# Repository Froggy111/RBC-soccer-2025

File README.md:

# RBC-soccer-2025

(Currently internal) Repository for 2025 RCJ Soccer Lightweight team from RI.

Other Links:
- Component spreadsheet: https://docs.google.com/spreadsheets/d/1nkJU1fMwBykuh6vTQhCEh5VCzHdAhULuCZyUjWnpDP0/edit#gid=0

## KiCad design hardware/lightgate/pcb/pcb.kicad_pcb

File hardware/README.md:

- `./*.md`: General Information about Hardware
- `./{component}/*.md`: Information about a specific component

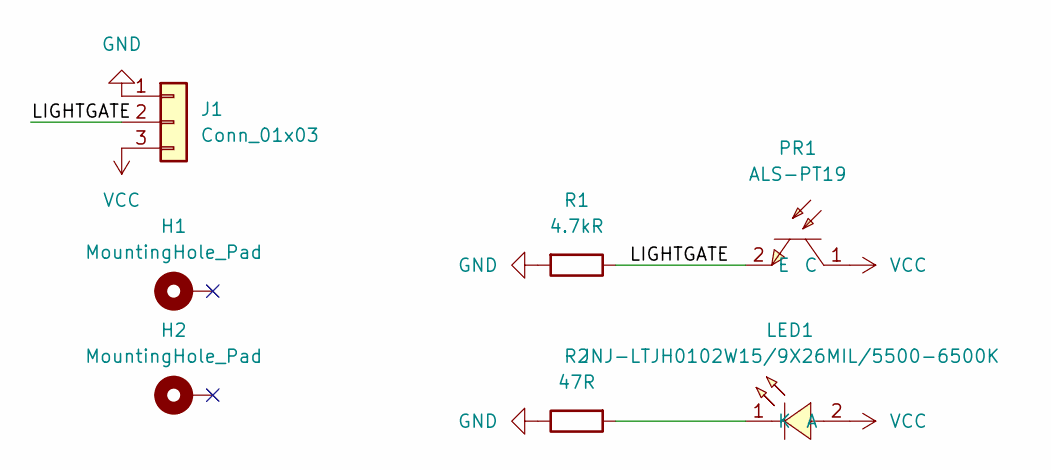
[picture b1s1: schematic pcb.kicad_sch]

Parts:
H1, H2: MountingHole_Pad; MountingHole_2.2mm_M2_Pad_Via
J1: Conn_01x03; JST_XH_B3B-XH-A_1x03_P2.50mm_Vertical
LED1: JNJ-LTJH0102W15/9X26MIL/5500-6500K; LED-SMD_L3.5-W2.8_JNJ-LTJH0111W60; LCSC Part C7500117
PR1: ALS-PT19; SENSORS-SMD_ALS-PT19; LCSC Part C146233
R1: 4.7kR; R_1206_3216Metric_Pad1.30x1.75mm_HandSolder
R2: 47R; R_1206_3216Metric_Pad1.30x1.75mm_HandSolder

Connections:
/LIGHTGATE: J1.2, PR1.2 (E), R1.1
GND: J1.1, R1.2, R2.1
unnamed: LED1.1 (K), R2.2
VCC: J1.3, LED1.2 (A), PR1.1 (C)

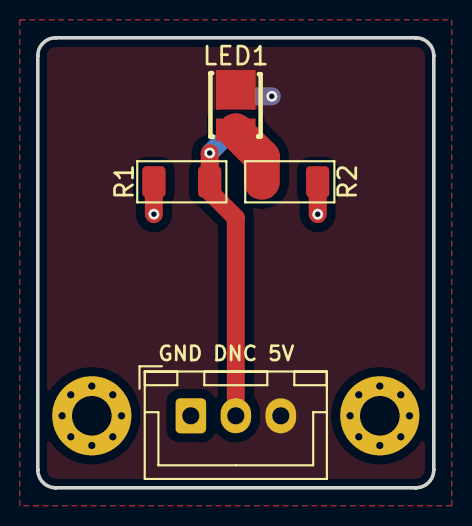
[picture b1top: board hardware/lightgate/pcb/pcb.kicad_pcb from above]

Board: 2 copper layers, 22.0 x 25.0 mm, 7 parts (1 on the bottom side), 4 nets.

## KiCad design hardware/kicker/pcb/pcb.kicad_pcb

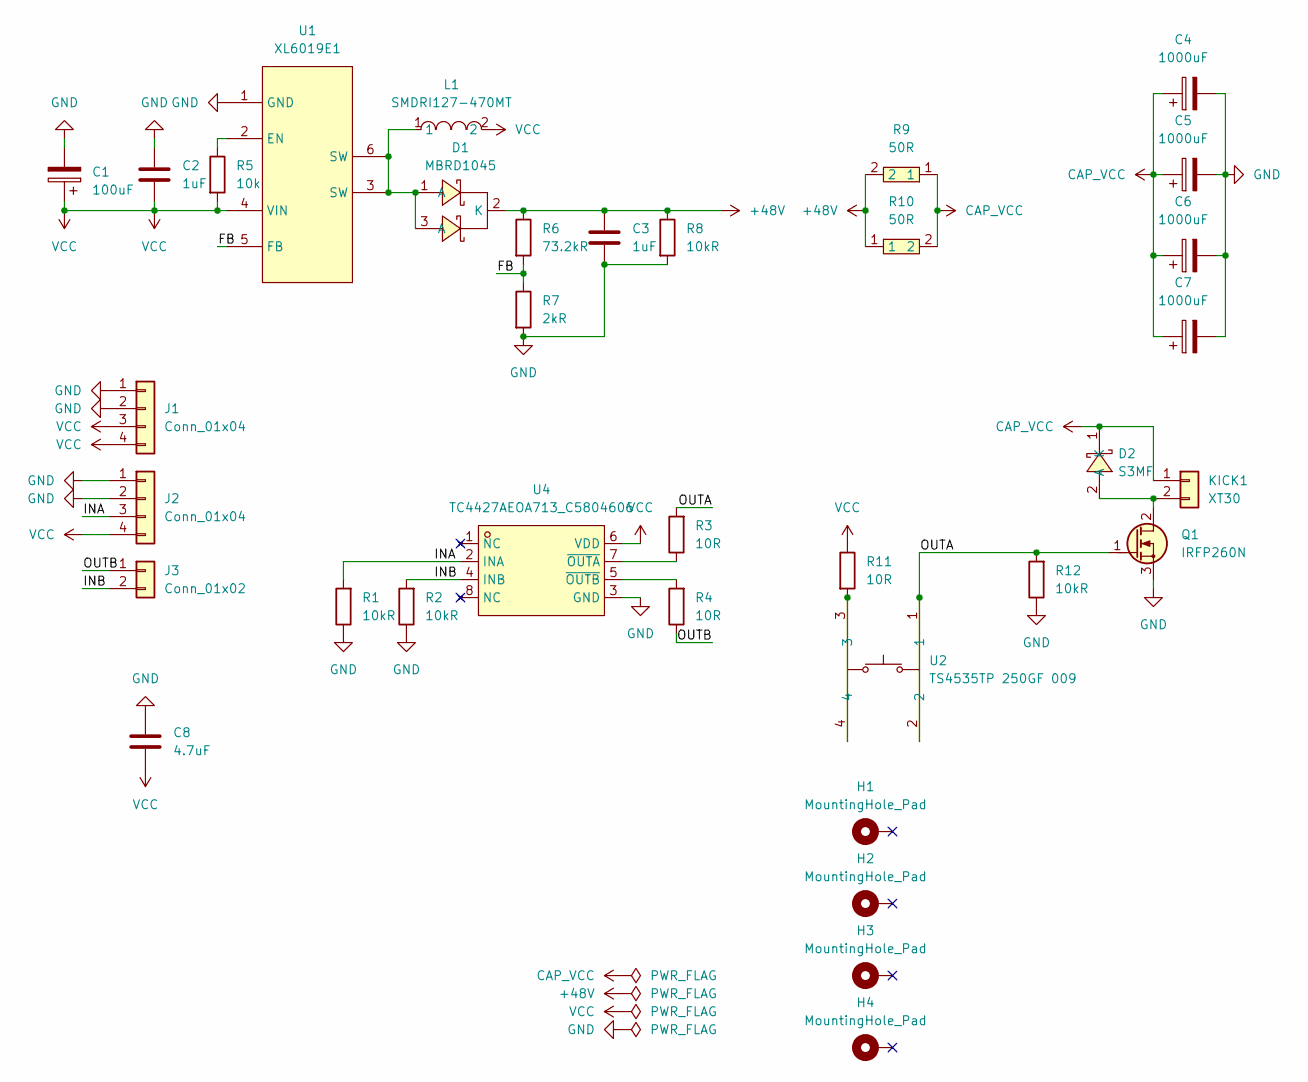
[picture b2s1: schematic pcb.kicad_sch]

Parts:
C1: 100uF; CP_Elec_6.3x7.7
C2, C3: 1uF; C_1206_3216Metric_Pad1.33x1.80mm_HandSolder
C4, C5, C6, C7: 1000uF; CAP-TH_BD13.0-P5.00-D1.2-FD
C8: 4.7uF; C_1206_3216Metric_Pad1.33x1.80mm_HandSolder
D1: MBRD1045; TO-252-3_L6.5-W5.9-P4.60-LS10.0-BL; LCSC Part C5137764
D2: S3MF; SMAF_L3.5-W2.6-LS4.7-RD-1; LCSC Part C18199092
H1, H2, H3, H4: MountingHole_Pad; MountingHole_2.2mm_M2_Pad_Via
J1, J2: Conn_01x04; PinHeader_1x04_P2.54mm_Vertical
J3: Conn_01x02; JST_PH_B2B-PH-K_1x02_P2.00mm_Vertical
KICK1: XT30; AMASS_XT30U-F_1x02_P5.0mm_Vertical
L1: SMDRI127-470MT; IND-SMD_L12.3-W12.3; LCSC Part C9906
Q1: IRFP260N; TO-247-3_Vertical_GDS
R1, R2, R8, R12: 10kR; R_1206_3216Metric_Pad1.30x1.75mm_HandSolder
R3, R4, R11: 10R; R_1206_3216Metric_Pad1.30x1.75mm_HandSolder
R5: 10k; R_1206_3216Metric_Pad1.30x1.75mm_HandSolder
R6: 73.2kR; R_1206_3216Metric_Pad1.30x1.75mm_HandSolder
R7: 2kR; R_1206_3216Metric_Pad1.30x1.75mm_HandSolder
R9, R10: 50R; TO-220-2L_L10.2-W4.6-P5.08-L; LCSC Part C5209737
U1: XL6019E1; TO-263-5_L10.2-W9.9-P1.70-LS14.4-TL; LCSC Part C73018
U2: TS4535TP 250GF 009; SW-SMD_4P-L4.5-W4.5-P3.00-LS6.8; LCSC Part C5342982
U4: TC4427AEOA713_C5804606; SOIC-8_L4.9-W3.9-P1.27-LS6.0-BL; LCSC Part C5804606

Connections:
+48V: C3.1, D1.2 (K), R6.1, R8.1, R9.2, R10.1
/FB: R6.2, R7.1, U1.5 (FB)
/INA: J2.3, R1.2, U4.2 (INA)
/INB: J3.2, R2.2, U4.4 (INB)
/OUTA: Q1.1 (G), R3.2, R12.2, U2.1, U2.2
/OUTB: J3.1, R4.1
CAP_VCC: C4.1, C5.1, C6.1, C7.1, D2.1 (K), KICK1.1, R9.1, R10.2
GND: C1.2, C2.1, C3.2, C4.2, C5.2, C6.2, C7.2, C8.1, J1.1, J1.2, J2.1, J2.2, Q1.3 (S), R1.1, R2.1, R7.2, R8.2, R12.1, U1.1 (GND), U4.3 (GND)
unnamed: D1.1 (A), D1.3 (A), L1.1, U1.3 (SW), U1.6 (SW)
unnamed: D2.2 (A), KICK1.2, Q1.2 (D)
unnamed: R11.2, U2.3, U2.4
unnamed: R5.1, U1.2 (EN)
unnamed: R3.1, U4.7 (~OUTA)
unnamed: R4.2, U4.5 (~OUTB)
VCC: C1.1, C2.2, C8.2, J1.3, J1.4, J2.4, L1.2, R5.2, R11.1, U1.4 (VIN), U4.6 (VDD)

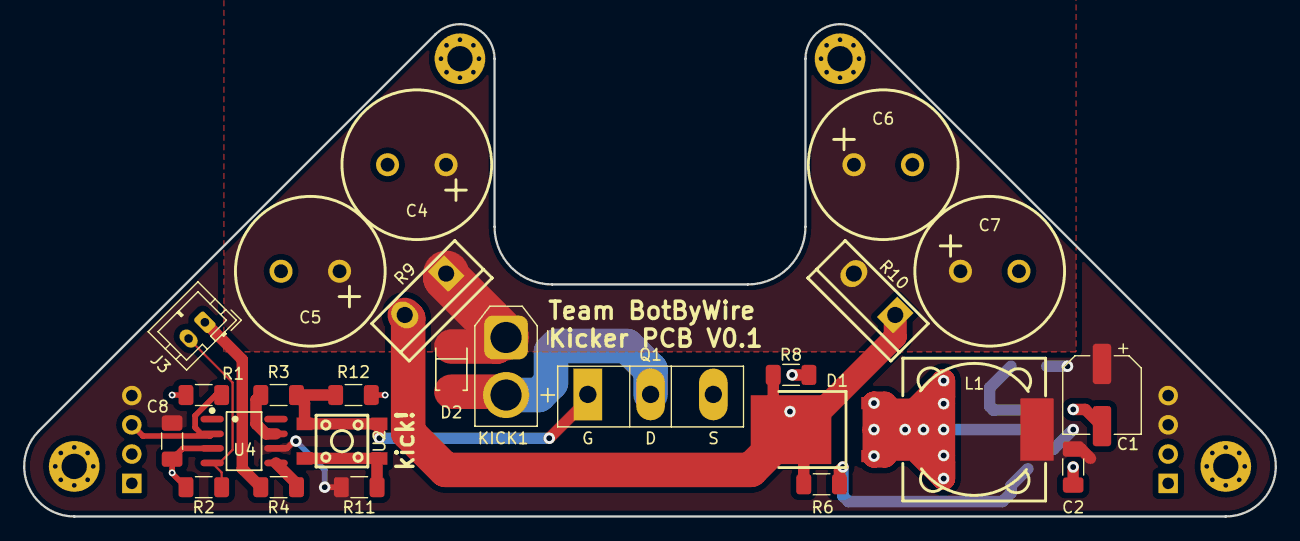
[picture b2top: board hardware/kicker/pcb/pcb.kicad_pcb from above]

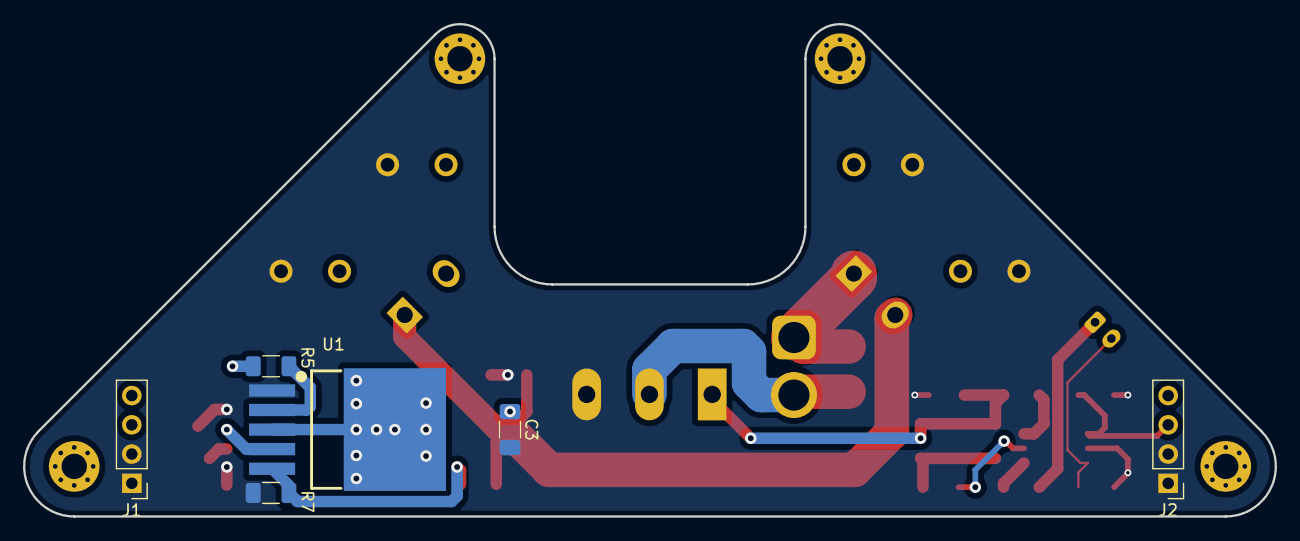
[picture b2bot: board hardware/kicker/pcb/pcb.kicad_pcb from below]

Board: 2 copper layers, 108.7 x 42.8 mm, 35 parts (6 on the bottom side), 15 nets.

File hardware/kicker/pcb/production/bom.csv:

Designator,Footprint,Quantity,Value,LCSC Part #
C1,CP_Elec_6.3x7.7,1,100uF,
"C2, C3",1206,2,1uF,
"C4, C5, C6, C7",CAP-TH_BD13.0-P5.00-D1.2-FD,4,1000uF,
C8,1206,1,4.7uF,
D1,TO-252-3_L6.5-W5.9-P4.60-LS10.0-BL,1,MBRD1045,C5137764
D2,SMAF_L3.5-W2.6-LS4.7-RD-1,1,S3MF,C18199092
"J1, J2",PinHeader_1x04_P2.54mm_Vertical,2,Conn_01x04,
J3,JST_PH_B2B-PH-K_1x02_P2.00mm_Vertical,1,Conn_01x02,
KICK1,AMASS_XT30U-F_1x02_P5.0mm_Vertical,1,XT30,
L1,IND-SMD_L12.3-W12.3,1,SMDRI127-470MT,C9906
Q1,TO-247-3_Vertical,1,NMOS,
"R1, R11, R12, R2, R8",1206,5,10kR,
"R10, R9",TO-220-2L_L10.2-W4.6-P5.08-L,2,50R,C5209737
"R3, R4",1206,2,10R,
R5,1206,1,10k,
R6,1206,1,73.2kR,
R7,1206,1,2kR,
U1,TO-263-5_L10.2-W9.9-P1.70-LS14.4-TL,1,XL6019E1,C73018
U2,SW-SMD_4P-L4.5-W4.5-P3.00-LS6.8,1,TS4535TP 250GF 009,C5342982
U4,SOIC-8_L4.9-W3.9-P1.27-LS6.0-BL,1,TC4427AEOA713_C5804606,C5804606

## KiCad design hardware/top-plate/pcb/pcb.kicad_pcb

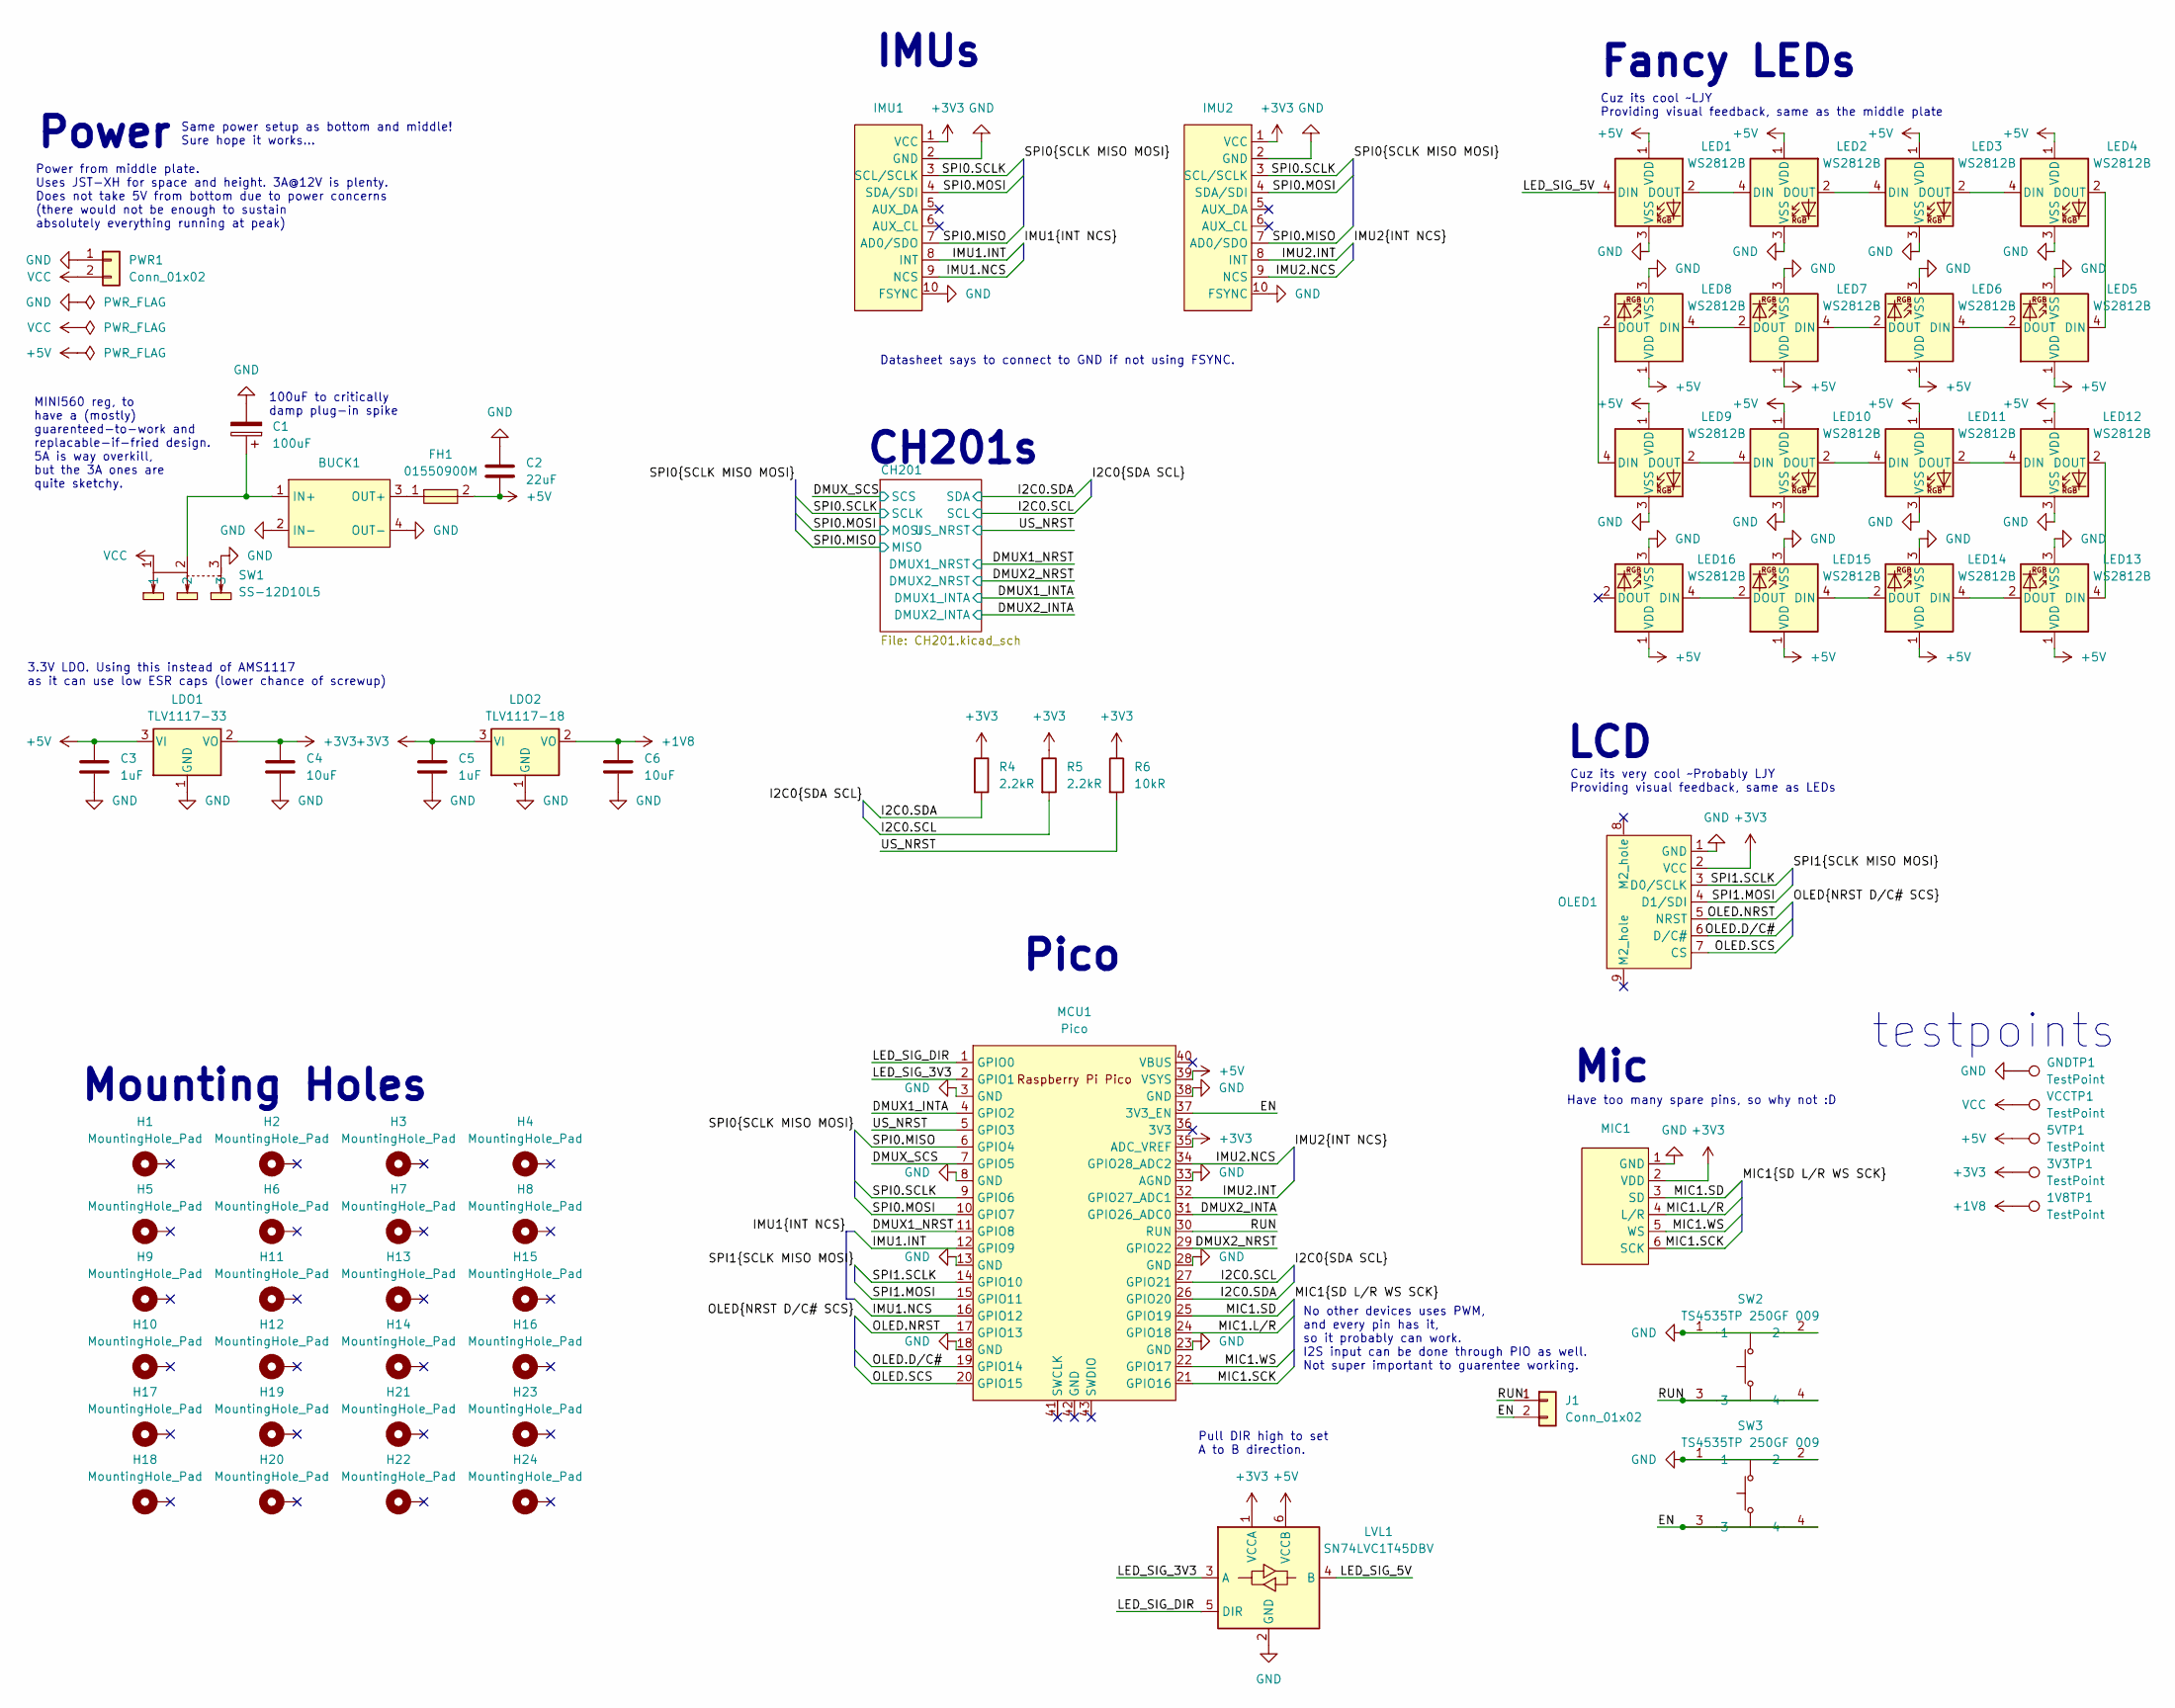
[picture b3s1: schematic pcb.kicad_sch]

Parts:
1V8TP1, 3V3TP1, 5VTP1: TestPoint; TestPoint_THTPad_D1.0mm_Drill0.5mm
BUCK1: mini560
C1: 100uF; CP_Elec_6.3x7.7
C2: 22uF; C_0805_2012Metric_Pad1.15x1.40mm_HandSolder
C3, C5: 1uF; C_0805_2012Metric_Pad1.15x1.40mm_HandSolder
C4, C6: 10uF; C_0805_2012Metric_Pad1.15x1.40mm_HandSolder
FH1: 01550900M; FUSE-SMD_L9.8-W5.0; LCSC Part C108518
GNDTP1: TestPoint; TestPoint_THTPad_D1.0mm_Drill0.5mm
H1, H2, H3, H4, H5, H6, H7, H8, H9, H10, H11, H12, H13, H14, H15, H16, H17, H18, H19, H20, H21, H22, H23, H24: MountingHole_Pad; MountingHole_2.2mm_M2_Pad_Via
IMU1, IMU2: ICM20948-no-mountingholes
J1: Conn_01x02; JST_XH_B2B-XH-A_1x02_P2.50mm_Vertical
LDO1: TLV1117-33; SOT-223-3_TabPin2
LDO2: TLV1117-18; SOT-223-3_TabPin2
LED1, LED2, LED3, LED4, LED5, LED6, LED7, LED8, LED9, LED10, LED11, LED12, LED13, LED14, LED15, LED16: WS2812B; LED_WS2812B_PLCC4_5.0x5.0mm_P3.2mm
LVL1: SN74LVC1T45DBV; SOT-23-6
MCU1: Pico; RPi_Pico_SMD_TH_USBC_cable_cutout
MIC1: INMP441_SMD
OLED1: 0.96-inch_OLED_7-no-back-mountingholes
PWR1: Conn_01x02; JST_XH_B2B-XH-A_1x02_P2.50mm_Vertical
R4, R5: 2.2kR; R_0805_2012Metric_Pad1.15x1.40mm_HandSolder
R6: 10kR; R_0805_2012Metric_Pad1.15x1.40mm_HandSolder
SW1: SS-12D10L5; SW-TH_SS-12D10L5; LCSC Part C319012
SW2, SW3: TS4535TP 250GF 009; SW-SMD_4P-L4.5-W4.5-P3.00-LS6.8; LCSC Part C5342982
VCCTP1: TestPoint; TestPoint_THTPad_D1.0mm_Drill0.5mm

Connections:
+1V8: 1V8TP1.1, C6.2, LDO2.2 (VO); also elsewhere on the board
+3V3: 3V3TP1.1, C4.2, C5.2, IMU1.1 (VCC), IMU2.1 (VCC), LDO1.2 (VO), LDO2.3 (VI), LVL1.1 (VCCA), MCU1.35 (ADC_VREF), MIC1.2 (VDD), OLED1.2 (VCC), R4.1, R5.1, R6.1; also elsewhere on the board
+5V: 5VTP1.1, C2.2, C3.2, FH1.2, LDO1.3 (VI), LED1.1 (VDD), LED2.1 (VDD), LED3.1 (VDD), LED4.1 (VDD), LED5.1 (VDD), LED6.1 (VDD), LED7.1 (VDD), LED8.1 (VDD), LED9.1 (VDD), LED10.1 (VDD), LED11.1 (VDD), LED12.1 (VDD), LED13.1 (VDD), LED14.1 (VDD), LED15.1 (VDD), LED16.1 (VDD), LVL1.6 (VCCB), MCU1.39 (VSYS)
/DMUX1_INTA: MCU1.4 (GPIO2); also elsewhere on the board
/DMUX1_NRST: MCU1.11 (GPIO8); also elsewhere on the board
/DMUX2_INTA: MCU1.31 (GPIO26_ADC0); also elsewhere on the board
/DMUX2_NRST: MCU1.29 (GPIO22); also elsewhere on the board
/DMUX_SCS: MCU1.7 (GPIO5); also elsewhere on the board
/EN: J1.2, MCU1.37 (3V3_EN), SW3.3, SW3.4
/I2C0.SCL: MCU1.27 (GPIO21), R5.2; also elsewhere on the board
/I2C0.SDA: MCU1.26 (GPIO20), R4.2; also elsewhere on the board
/IMU1.INT: IMU1.8 (INT), MCU1.12 (GPIO9)
/IMU1.NCS: IMU1.9 (NCS), MCU1.16 (GPIO12)
/IMU2.INT: IMU2.8 (INT), MCU1.32 (GPIO27_ADC1)
/IMU2.NCS: IMU2.9 (NCS), MCU1.34 (GPIO28_ADC2)
/LED_SIG_3V3: LVL1.3 (A), MCU1.2 (GPIO1)
/LED_SIG_5V: LED1.4 (DIN), LVL1.4 (B)
/LED_SIG_DIR: LVL1.5 (DIR), MCU1.1 (GPIO0)
/MIC1.L/R: MCU1.24 (GPIO18), MIC1.4 (L/R)
/MIC1.SCK: MCU1.21 (GPIO16), MIC1.6 (SCK)
/MIC1.SD: MCU1.25 (GPIO19), MIC1.3 (SD)
/MIC1.WS: MCU1.22 (GPIO17), MIC1.5 (WS)
/OLED.D/C#: MCU1.19 (GPIO14), OLED1.6 (D/C#)
/OLED.NRST: MCU1.17 (GPIO13), OLED1.5 (NRST)
/OLED.SCS: MCU1.20 (GPIO15), OLED1.7 (CS)
/RUN: J1.1, MCU1.30 (RUN), SW2.3, SW2.4
/SPI0.MISO: IMU1.7 (AD0/SDO), IMU2.7 (AD0/SDO), MCU1.6 (GPIO4); also elsewhere on the board
/SPI0.MOSI: IMU1.4 (SDA/SDI), IMU2.4 (SDA/SDI), MCU1.10 (GPIO7); also elsewhere on the board
/SPI0.SCLK: IMU1.3 (SCL/SCLK), IMU2.3 (SCL/SCLK), MCU1.9 (GPIO6); also elsewhere on the board
/SPI1.MOSI: MCU1.15 (GPIO11), OLED1.4 (D1/SDI)
/SPI1.SCLK: MCU1.14 (GPIO10), OLED1.3 (D0/SCLK)
/US_NRST: MCU1.5 (GPIO3), R6.2; also elsewhere on the board
GND: BUCK1.2 (IN-), BUCK1.4 (OUT-), C1.2, C2.1, C3.1, C4.1, C5.1, C6.1, GNDTP1.1, IMU1.2 (GND), IMU1.10 (FSYNC), IMU2.2 (GND), IMU2.10 (FSYNC), LDO1.1 (GND), LDO2.1 (GND), LED1.3 (VSS), LED2.3 (VSS), LED3.3 (VSS), LED4.3 (VSS), LED5.3 (VSS), LED6.3 (VSS), LED7.3 (VSS), LED8.3 (VSS), LED9.3 (VSS), LED10.3 (VSS), LED11.3 (VSS), LED12.3 (VSS), LED13.3 (VSS), LED14.3 (VSS), LED15.3 (VSS), LED16.3 (VSS), LVL1.2 (GND), MCU1.3 (GND), MCU1.8 (GND), MCU1.13 (GND), MCU1.18 (GND), MCU1.23 (GND), MCU1.28 (GND), MCU1.33 (AGND), MCU1.38 (GND), MIC1.1 (GND), OLED1.1 (GND), PWR1.1, SW1.3, SW2.1, SW2.2, SW3.1, SW3.2; also elsewhere on the board
unnamed: BUCK1.1 (IN+), C1.1, SW1.2
unnamed: BUCK1.3 (OUT+), FH1.1
unnamed: LED1.2 (DOUT), LED2.4 (DIN)
unnamed: LED2.2 (DOUT), LED3.4 (DIN)
unnamed: LED3.2 (DOUT), LED4.4 (DIN)
unnamed: LED4.2 (DOUT), LED5.4 (DIN)
unnamed: LED5.2 (DOUT), LED6.4 (DIN)
unnamed: LED6.2 (DOUT), LED7.4 (DIN)
unnamed: LED7.2 (DOUT), LED8.4 (DIN)
unnamed: LED8.2 (DOUT), LED9.4 (DIN)
unnamed: LED9.2 (DOUT), LED10.4 (DIN)
unnamed: LED10.2 (DOUT), LED11.4 (DIN)
unnamed: LED11.2 (DOUT), LED12.4 (DIN)
unnamed: LED12.2 (DOUT), LED13.4 (DIN)
unnamed: LED13.2 (DOUT), LED14.4 (DIN)
unnamed: LED14.2 (DOUT), LED15.4 (DIN)
unnamed: LED15.2 (DOUT), LED16.4 (DIN)
VCC: PWR1.2, SW1.1, VCCTP1.1

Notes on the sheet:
CH201s
IMUs
No other devices uses PWM, and every pin has it, so it probably can work. I2S input can be done through PIO as well. Not super important to guarentee working.
MINI560 reg, to have a (mostly) guarenteed-to-work and replacable-if-fried design. 5A is way overkill, but the 3A ones are quite sketchy.
Same power setup as bottom and middle! Sure hope it works...
Cuz its very cool ~Probably LJY Providing visual feedback, same as LEDs
Fancy LEDs
3.3V LDO. Using this instead of AMS1117 as it can use low ESR caps (lower chance of screwup)
Datasheet says to connect to GND if not using FSYNC.
Pull DIR high to set A to B direction.
Have too many spare pins, so why not :D
Cuz its cool ~LJY Providing visual feedback, same as the middle plate
Power
Pico
Power from middle plate. Uses JST-XH for space and height. 3A@12V is plenty. Does not take 5V from bottom due to power concerns (there would not be enough to sustain absolutely everything running at peak)
100uF to critically damp plug-in spike
Mic
LCD
Mounting Holes
testpoints

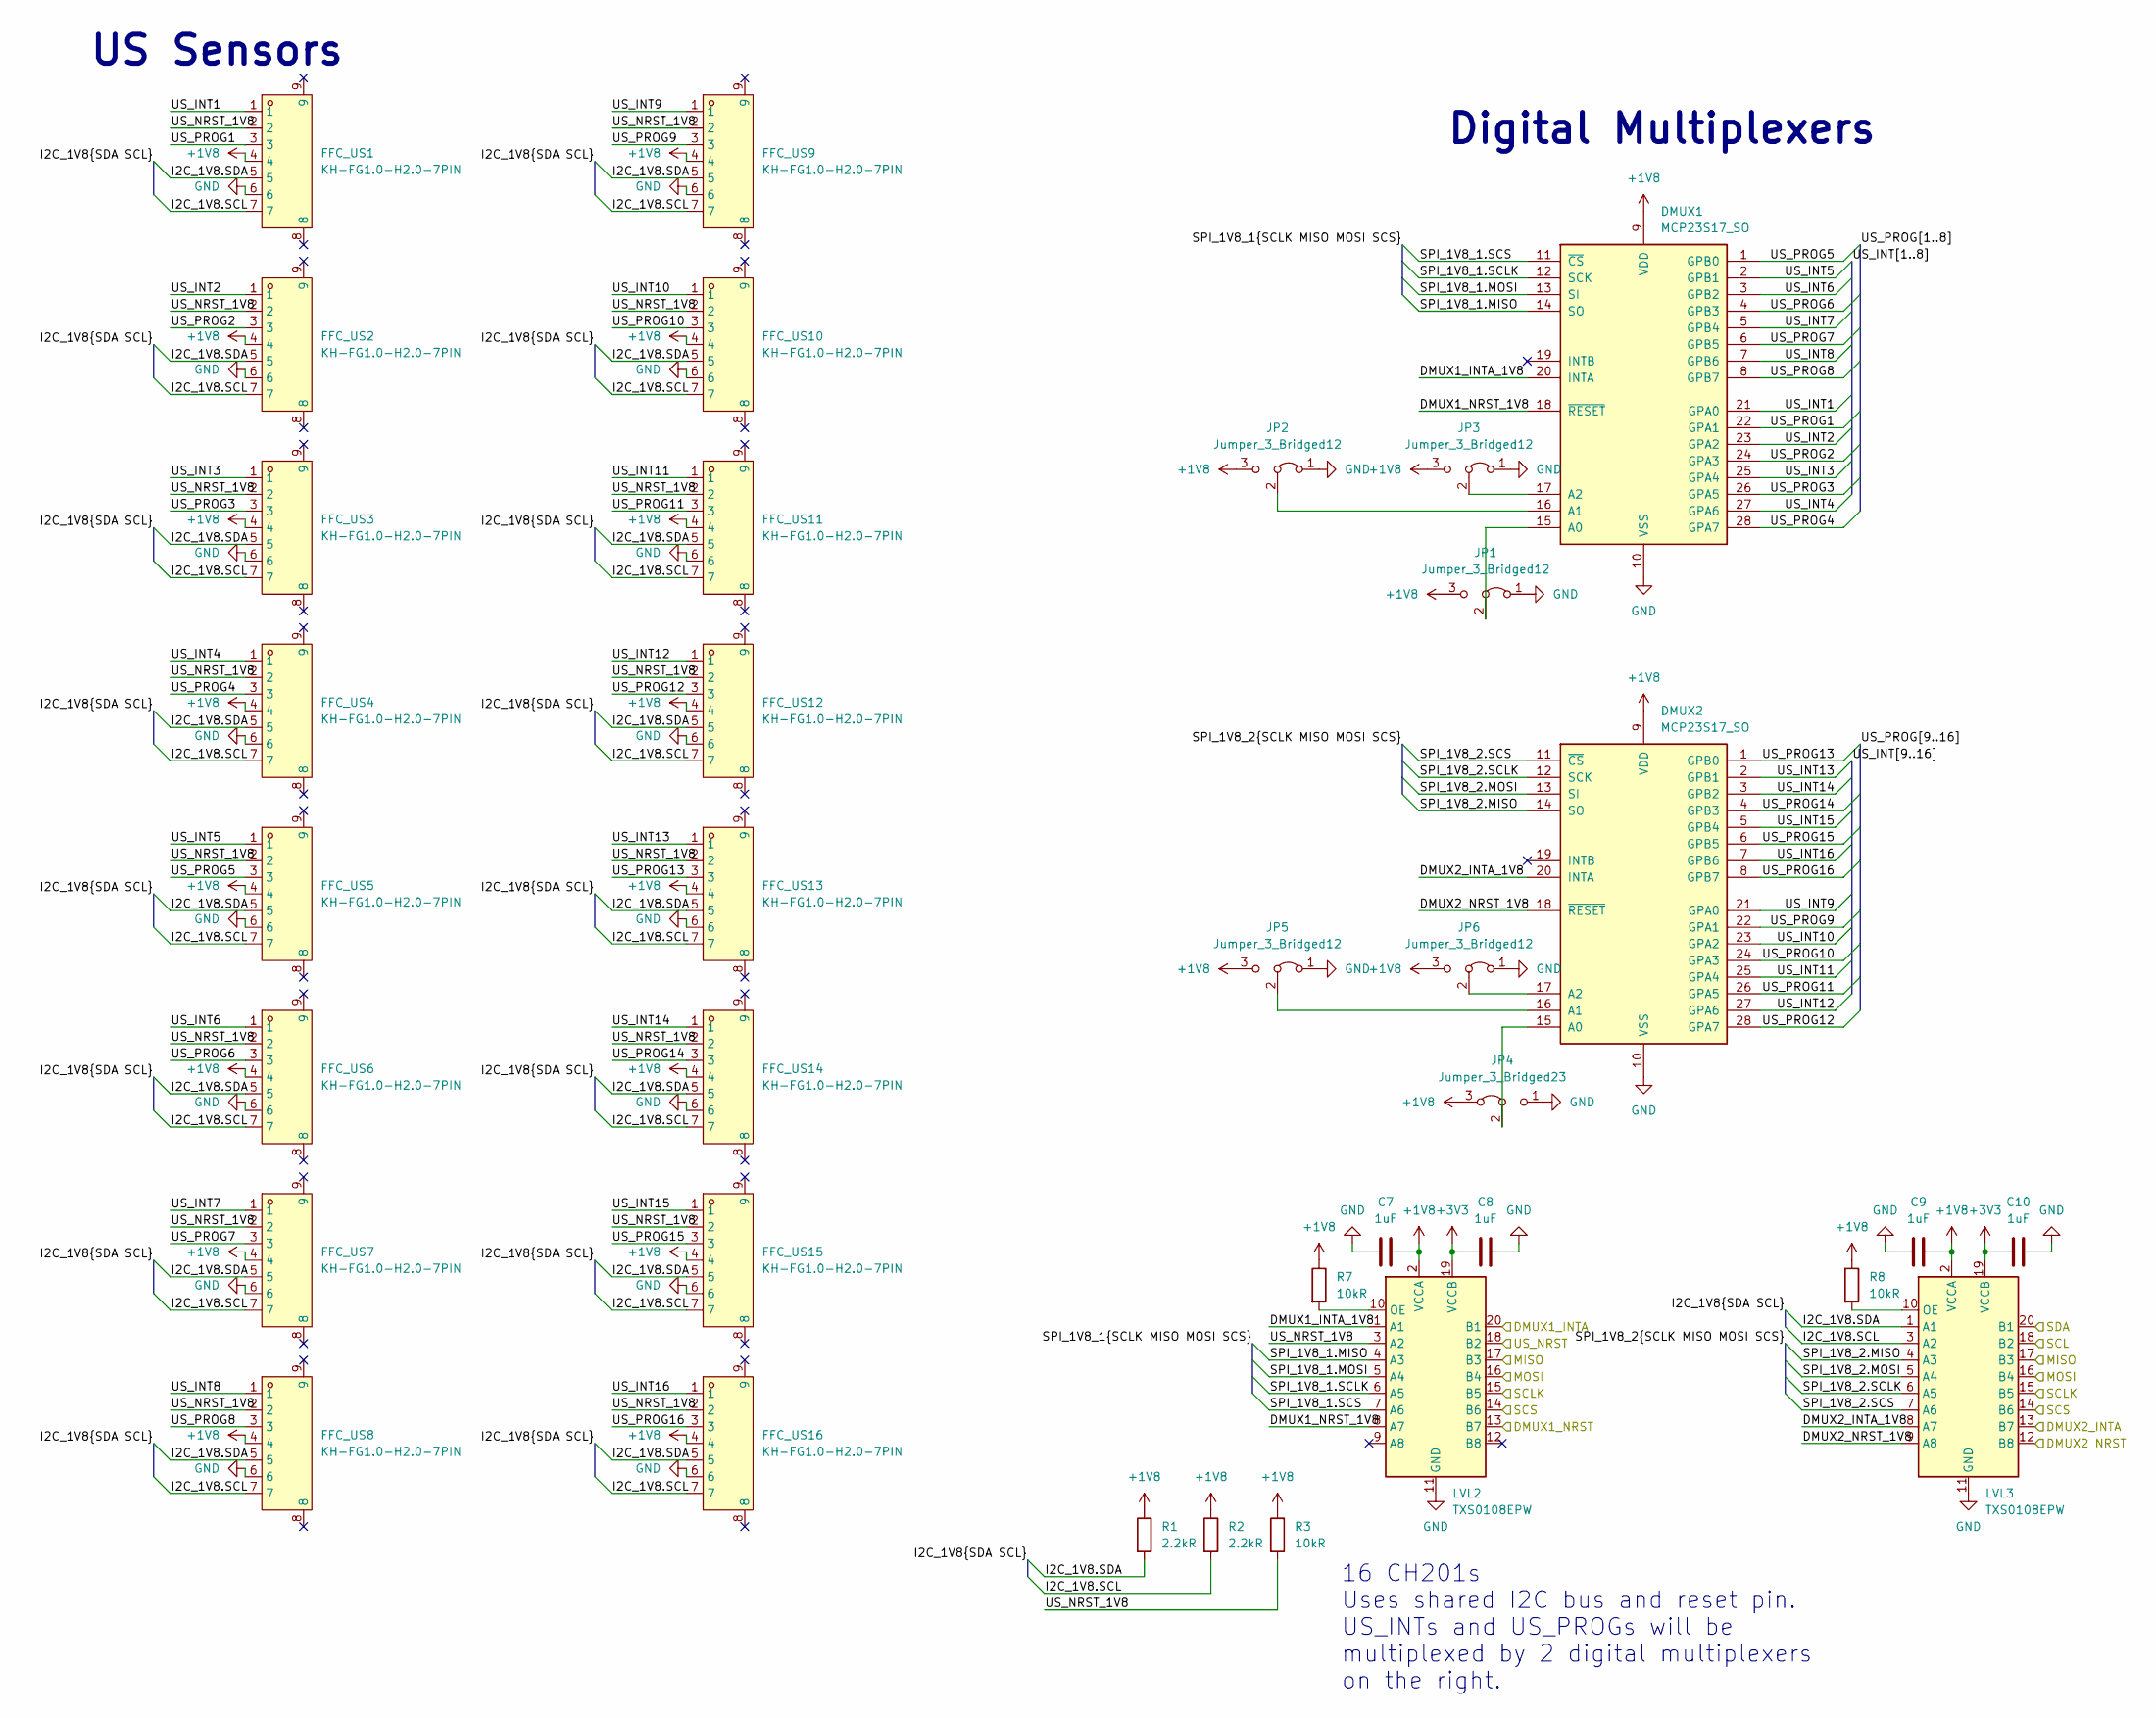
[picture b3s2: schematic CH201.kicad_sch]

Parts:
C7, C8, C9, C10: 1uF; C_0805_2012Metric_Pad1.15x1.40mm_HandSolder
DMUX1, DMUX2: MCP23S17_SO; SOIC-28W_7.5x17.9mm_P1.27mm
FFC_US1, FFC_US2, FFC_US3, FFC_US4, FFC_US5, FFC_US6, FFC_US7, FFC_US8, FFC_US9, FFC_US10, FFC_US11, FFC_US12, FFC_US13, FFC_US14, FFC_US15, FFC_US16: KH-FG1.0-H2.0-7PIN; FPC-SMD_7P-P1.0_KINGHELM_KH-FG1.0-H2.0-7PIN; LCSC Part C2925379
JP1, JP2, JP3, JP5, JP6: Jumper_3_Bridged12; PinHeader_1x03_P1.27mm_Vertical
JP4: Jumper_3_Bridged23; PinHeader_1x03_P1.27mm_Vertical
LVL2, LVL3: TXS0108EPW; TSSOP-20_4.4x6.5mm_P0.65mm
R1, R2: 2.2kR; R_0805_2012Metric_Pad1.15x1.40mm_HandSolder
R3, R7, R8: 10kR; R_0805_2012Metric_Pad1.15x1.40mm_HandSolder

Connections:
+1V8: C7.2, C9.2, DMUX1.9 (VDD), DMUX2.9 (VDD), FFC_US1.4, FFC_US2.4, FFC_US3.4, FFC_US4.4, FFC_US5.4, FFC_US6.4, FFC_US7.4, FFC_US8.4, FFC_US9.4, FFC_US10.4, FFC_US11.4, FFC_US12.4, FFC_US13.4, FFC_US14.4, FFC_US15.4, FFC_US16.4, JP1.3 (B), JP2.3 (B), JP3.3 (B), JP4.3 (A), JP5.3 (B), JP6.3 (B), LVL2.2 (VCCA), LVL3.2 (VCCA), R1.1, R2.1, R3.1, R7.1, R8.1; also elsewhere on the board
+3V3: C8.1, C10.1, LVL2.19 (VCCB), LVL3.19 (VCCB); also elsewhere on the board
/CH201/DMUX1_INTA_1V8: DMUX1.20 (INTA), LVL2.1 (A1)
/CH201/DMUX1_NRST_1V8: DMUX1.18 (~RESET), LVL2.8 (A7)
/CH201/DMUX2_INTA_1V8: DMUX2.20 (INTA), LVL3.8 (A7)
/CH201/DMUX2_NRST_1V8: DMUX2.18 (~RESET), LVL3.9 (A8)
/CH201/I2C_1V8.SCL: FFC_US1.7, FFC_US2.7, FFC_US3.7, FFC_US4.7, FFC_US5.7, FFC_US6.7, FFC_US7.7, FFC_US8.7, FFC_US9.7, FFC_US10.7, FFC_US11.7, FFC_US12.7, FFC_US13.7, FFC_US14.7, FFC_US15.7, FFC_US16.7, LVL3.3 (A2), R2.2
/CH201/I2C_1V8.SDA: FFC_US1.5, FFC_US2.5, FFC_US3.5, FFC_US4.5, FFC_US5.5, FFC_US6.5, FFC_US7.5, FFC_US8.5, FFC_US9.5, FFC_US10.5, FFC_US11.5, FFC_US12.5, FFC_US13.5, FFC_US14.5, FFC_US15.5, FFC_US16.5, LVL3.1 (A1), R1.2
/CH201/SPI_1V8_1.MISO: DMUX1.14 (SO), LVL2.4 (A3)
/CH201/SPI_1V8_1.MOSI: DMUX1.13 (SI), LVL2.5 (A4)
/CH201/SPI_1V8_1.SCLK: DMUX1.12 (SCK), LVL2.6 (A5)
/CH201/SPI_1V8_1.SCS: DMUX1.11 (~CS), LVL2.7 (A6)
/CH201/SPI_1V8_2.MISO: DMUX2.14 (SO), LVL3.4 (A3)
/CH201/SPI_1V8_2.MOSI: DMUX2.13 (SI), LVL3.5 (A4)
/CH201/SPI_1V8_2.SCLK: DMUX2.12 (SCK), LVL3.6 (A5)
/CH201/SPI_1V8_2.SCS: DMUX2.11 (~CS), LVL3.7 (A6)
/CH201/US_INT1: DMUX1.21 (GPA0), FFC_US1.1
/CH201/US_INT2: DMUX1.23 (GPA2), FFC_US2.1
/CH201/US_INT3: DMUX1.25 (GPA4), FFC_US3.1
/CH201/US_INT4: DMUX1.27 (GPA6), FFC_US4.1
/CH201/US_INT5: DMUX1.2 (GPB1), FFC_US5.1
/CH201/US_INT6: DMUX1.3 (GPB2), FFC_US6.1
/CH201/US_INT7: DMUX1.5 (GPB4), FFC_US7.1
/CH201/US_INT8: DMUX1.7 (GPB6), FFC_US8.1
/CH201/US_INT9: DMUX2.21 (GPA0), FFC_US9.1
/CH201/US_INT10: DMUX2.23 (GPA2), FFC_US10.1
/CH201/US_INT11: DMUX2.25 (GPA4), FFC_US11.1
/CH201/US_INT12: DMUX2.27 (GPA6), FFC_US12.1
/CH201/US_INT13: DMUX2.2 (GPB1), FFC_US13.1
/CH201/US_INT14: DMUX2.3 (GPB2), FFC_US14.1
/CH201/US_INT15: DMUX2.5 (GPB4), FFC_US15.1
/CH201/US_INT16: DMUX2.7 (GPB6), FFC_US16.1
/CH201/US_NRST_1V8: FFC_US1.2, FFC_US2.2, FFC_US3.2, FFC_US4.2, FFC_US5.2, FFC_US6.2, FFC_US7.2, FFC_US8.2, FFC_US9.2, FFC_US10.2, FFC_US11.2, FFC_US12.2, FFC_US13.2, FFC_US14.2, FFC_US15.2, FFC_US16.2, LVL2.3 (A2), R3.2
/CH201/US_PROG1: DMUX1.22 (GPA1), FFC_US1.3
/CH201/US_PROG2: DMUX1.24 (GPA3), FFC_US2.3
/CH201/US_PROG3: DMUX1.26 (GPA5), FFC_US3.3
/CH201/US_PROG4: DMUX1.28 (GPA7), FFC_US4.3
/CH201/US_PROG5: DMUX1.1 (GPB0), FFC_US5.3
/CH201/US_PROG6: DMUX1.4 (GPB3), FFC_US6.3
/CH201/US_PROG7: DMUX1.6 (GPB5), FFC_US7.3
/CH201/US_PROG8: DMUX1.8 (GPB7), FFC_US8.3
/CH201/US_PROG9: DMUX2.22 (GPA1), FFC_US9.3
/CH201/US_PROG10: DMUX2.24 (GPA3), FFC_US10.3
/CH201/US_PROG11: DMUX2.26 (GPA5), FFC_US11.3
/CH201/US_PROG12: DMUX2.28 (GPA7), FFC_US12.3
/CH201/US_PROG13: DMUX2.1 (GPB0), FFC_US13.3
/CH201/US_PROG14: DMUX2.4 (GPB3), FFC_US14.3
/CH201/US_PROG15: DMUX2.6 (GPB5), FFC_US15.3
/CH201/US_PROG16: DMUX2.8 (GPB7), FFC_US16.3
/DMUX1_INTA: LVL2.20 (B1); also elsewhere on the board
/DMUX1_NRST: LVL2.13 (B7); also elsewhere on the board
/DMUX2_INTA: LVL3.13 (B7); also elsewhere on the board
/DMUX2_NRST: LVL3.12 (B8); also elsewhere on the board
/DMUX_SCS: LVL2.14 (B6), LVL3.14 (B6); also elsewhere on the board
/I2C0.SCL: LVL3.18 (B2); also elsewhere on the board
/I2C0.SDA: LVL3.20 (B1); also elsewhere on the board
/SPI0.MISO: LVL2.17 (B3), LVL3.17 (B3); also elsewhere on the board
/SPI0.MOSI: LVL2.16 (B4), LVL3.16 (B4); also elsewhere on the board
/SPI0.SCLK: LVL2.15 (B5), LVL3.15 (B5); also elsewhere on the board
/US_NRST: LVL2.18 (B2); also elsewhere on the board
GND: C7.1, C8.2, C9.1, C10.2, DMUX1.10 (VSS), DMUX2.10 (VSS), FFC_US1.6, FFC_US2.6, FFC_US3.6, FFC_US4.6, FFC_US5.6, FFC_US6.6, FFC_US7.6, FFC_US8.6, FFC_US9.6, FFC_US10.6, FFC_US11.6, FFC_US12.6, FFC_US13.6, FFC_US14.6, FFC_US15.6, FFC_US16.6, JP1.1 (A), JP2.1 (A), JP3.1 (A), JP4.1 (B), JP5.1 (A), JP6.1 (A), LVL2.11 (GND), LVL3.11 (GND); also elsewhere on the board
unnamed: DMUX1.15 (A0), JP1.2 (C)
unnamed: DMUX1.16 (A1), JP2.2 (C)
unnamed: DMUX1.17 (A2), JP3.2 (C)
unnamed: DMUX2.15 (A0), JP4.2 (C)
unnamed: DMUX2.16 (A1), JP5.2 (C)
unnamed: DMUX2.17 (A2), JP6.2 (C)
unnamed: LVL2.10 (OE), R7.2
unnamed: LVL3.10 (OE), R8.2

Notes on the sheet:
US Sensors
16 CH201s Uses shared I2C bus and reset pin. US_INTs and US_PROGs will be multiplexed by 2 digital multiplexers on the right.
Digital Multiplexers
